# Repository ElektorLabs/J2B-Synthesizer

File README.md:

J2B Synthesizer
===============

An open source, open hardware music synthesizer for you to enjoy.
Based on an LPC1347 32-bit ARM Cortex-M3 microcontroller, this synthesizer
uses PWM to output sound. Originally based on and inspired by the Soulsby
Atmegatron.

Software is an LPCXpresso project.

Precompiled binaries are included for several synthesizers including
one drum machine. Uploading the firmware to the microcontroller is as simple 
as copying a file to a USB stick (this works on Windows only).

Licensed as described in the diverse licenses that may be found in the
repository. Roughly they state that you are allowed to do whatever you want
with this, as long as it remains for private use. However, you are allowed
to make money from music made with the J2B Synthesizer. 

More info:

www.elektor-labs.com/j2b-synthesizer

This is Elektor project 140182, published in Elektor Magazine, January 2015.

www.elektor-magazine.com/140182

www.elektor.com

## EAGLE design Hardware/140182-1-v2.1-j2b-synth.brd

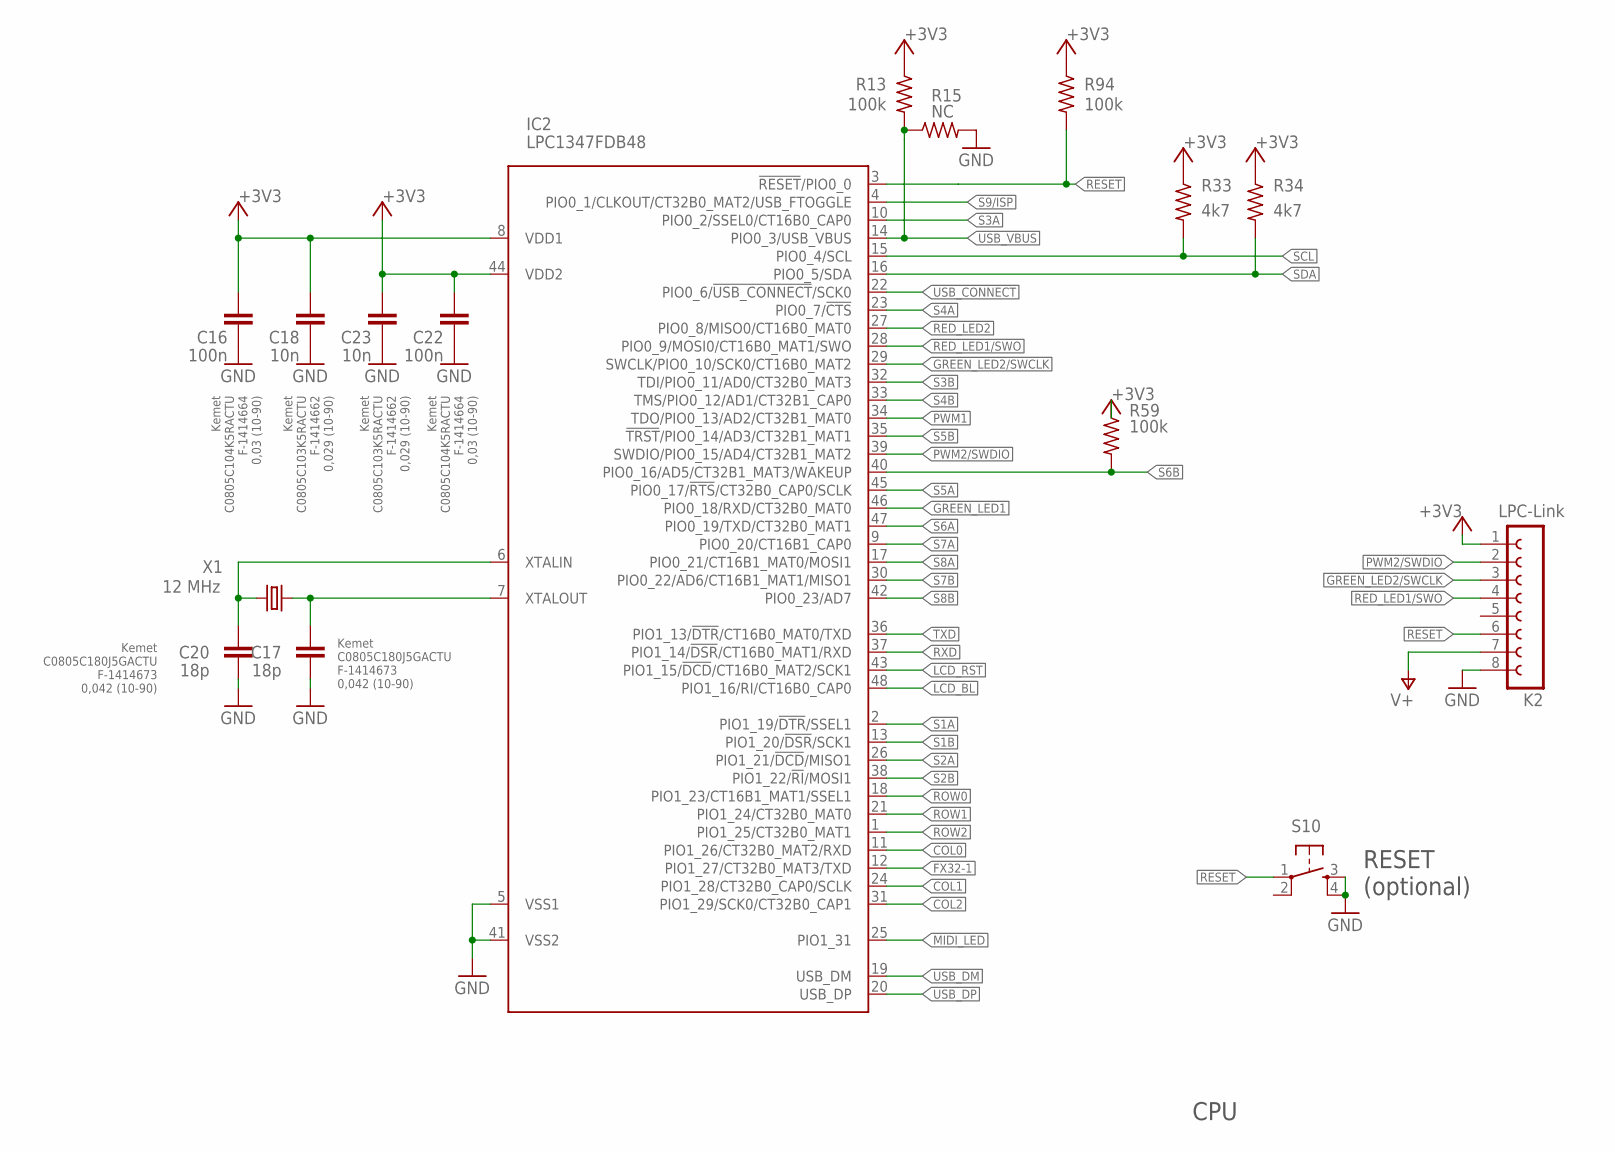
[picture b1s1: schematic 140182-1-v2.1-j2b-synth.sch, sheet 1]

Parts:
C16, C22: 100n; C0805K; FARNELL F-1414664
C17, C20: 18p; C0805K; FARNELL F-1414673
C18, C23: 10n; C0805K; FARNELL F-1414662
IC2: LPC1347FDB48; LQFP48
K2: LPC-Link; FE08
R13, R59, R94: 100k; R0805; FARNELL F-9333738
R15: NC; R0805
R33, R34: 4k7; R0805; FARNELL F-9334580
S10: S-TACTILE-6X6-PTH; EPP-S-TACT-6X6
X1: 12 MHz; SM49

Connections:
!GREEN_LED1!: IC2.46 (PIO0_18/RXD/CT32B0_MAT0); also elsewhere on the board
!GREEN_LED2!/SWCLK: IC2.29 (SWCLK/PIO0_10/SCK0/CT16B0_MAT2), K2.3; also elsewhere on the board
!LCD_BL: IC2.48 (PIO1_16/RI/CT16B0_CAP0); also elsewhere on the board
!RED_LED1!/SWO: IC2.28 (PIO0_9/MOSI0/CT16B0_MAT1/SWO), K2.4; also elsewhere on the board
!RED_LED2: IC2.27 (PIO0_8/MISO0/CT16B0_MAT0); also elsewhere on the board
!RESET: IC2.3 (!RESET!/PIO0_0), K2.6, R94.2, S10.1
!USB_CONNECT: IC2.22 (PIO0_6/!USB_CONNECT!/SCK0); also elsewhere on the board
+3V3: C16.2, C18.2, C22.2, C23.2, IC2.8 (VDD1), IC2.44 (VDD2), K2.1, R13.1, R33.1, R34.1, R59.1, R94.1; also elsewhere on the board
+5V: K2.7; also elsewhere on the board
COL0: IC2.11 (PIO1_26/CT32B0_MAT2/RXD); also elsewhere on the board
COL1: IC2.24 (PIO1_28/CT32B0_CAP0/SCLK); also elsewhere on the board
COL2: IC2.31 (PIO1_29/SCK0/CT32B0_CAP1); also elsewhere on the board
FX32-1: IC2.12 (PIO1_27/CT32B0_MAT3/TXD); also elsewhere on the board
GND: C16.1, C17.1, C18.1, C20.1, C22.1, C23.1, IC2.5 (VSS1), IC2.41 (VSS2), K2.8, R15.2, S10.3, S10.4; also elsewhere on the board
LCD_RST: IC2.43 (PIO1_15/!DCD!/CT16B0_MAT2/SCK1); also elsewhere on the board
MIDI_LED: IC2.25 (PIO1_31); also elsewhere on the board
unnamed: C20.2, IC2.6 (XTALIN), X1.1
unnamed: C17.2, IC2.7 (XTALOUT), X1.2
PWM1: IC2.34 (TDO/PIO0_13/AD2/CT32B1_MAT0); also elsewhere on the board
PWM2/SWDIO: IC2.39 (SWDIO/PIO0_15/AD4/CT32B1_MAT2), K2.2; also elsewhere on the board
ROW0: IC2.18 (PIO1_23/CT16B1_MAT1/SSEL1); also elsewhere on the board
ROW1: IC2.21 (PIO1_24/CT32B0_MAT0); also elsewhere on the board
ROW2: IC2.1 (PIO1_25/CT32B0_MAT1); also elsewhere on the board
RXD: IC2.37 (PIO1_14/!DSR!/CT16B0_MAT1/RXD); also elsewhere on the board
S1A: IC2.2 (PIO1_19/!DTR!/SSEL1); also elsewhere on the board
S1B: IC2.13 (PIO1_20/!DSR!/SCK1); also elsewhere on the board
S2A: IC2.26 (PIO1_21/!DCD!/MISO1); also elsewhere on the board
S2B: IC2.38 (PIO1_22/!RI!/MOSI1); also elsewhere on the board
S3A: IC2.10 (PIO0_2/SSEL0/CT16B0_CAP0); also elsewhere on the board
S3B: IC2.32 (TDI/PIO0_11/AD0/CT32B0_MAT3); also elsewhere on the board
S4A: IC2.23 (PIO0_7/!CTS); also elsewhere on the board
S4B: IC2.33 (TMS/PIO0_12/AD1/CT32B1_CAP0); also elsewhere on the board
S5A: IC2.45 (PIO0_17/!RTS!/CT32B0_CAP0/SCLK); also elsewhere on the board
S5B: IC2.35 (!TRST!/PIO0_14/AD3/CT32B1_MAT1); also elsewhere on the board
S6A: IC2.47 (PIO0_19/TXD/CT32B0_MAT1); also elsewhere on the board
S6B: IC2.40 (PIO0_16/AD5/CT32B1_MAT3/WAKEUP), R59.2; also elsewhere on the board
S7A: IC2.9 (PIO0_20/CT16B1_CAP0); also elsewhere on the board
S7B: IC2.30 (PIO0_22/AD6/CT16B1_MAT1/MISO1); also elsewhere on the board
S8A: IC2.17 (PIO0_21/CT16B1_MAT0/MOSI1); also elsewhere on the board
S8B: IC2.42 (PIO0_23/AD7); also elsewhere on the board
S9/ISP: IC2.4 (PIO0_1/CLKOUT/CT32B0_MAT2/USB_FTOGGLE); also elsewhere on the board
SCL: IC2.15 (PIO0_4/SCL), R33.2; also elsewhere on the board
SDA: IC2.16 (PIO0_5/SDA), R34.2; also elsewhere on the board
TXD: IC2.36 (PIO1_13/!DTR!/CT16B0_MAT0/TXD); also elsewhere on the board
USB_DM: IC2.19 (USB_DM); also elsewhere on the board
USB_DP: IC2.20 (USB_DP); also elsewhere on the board
USB_VBUS: IC2.14 (PIO0_3/USB_VBUS), R13.2, R15.1; also elsewhere on the board

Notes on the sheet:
CPU
RESET (optional)

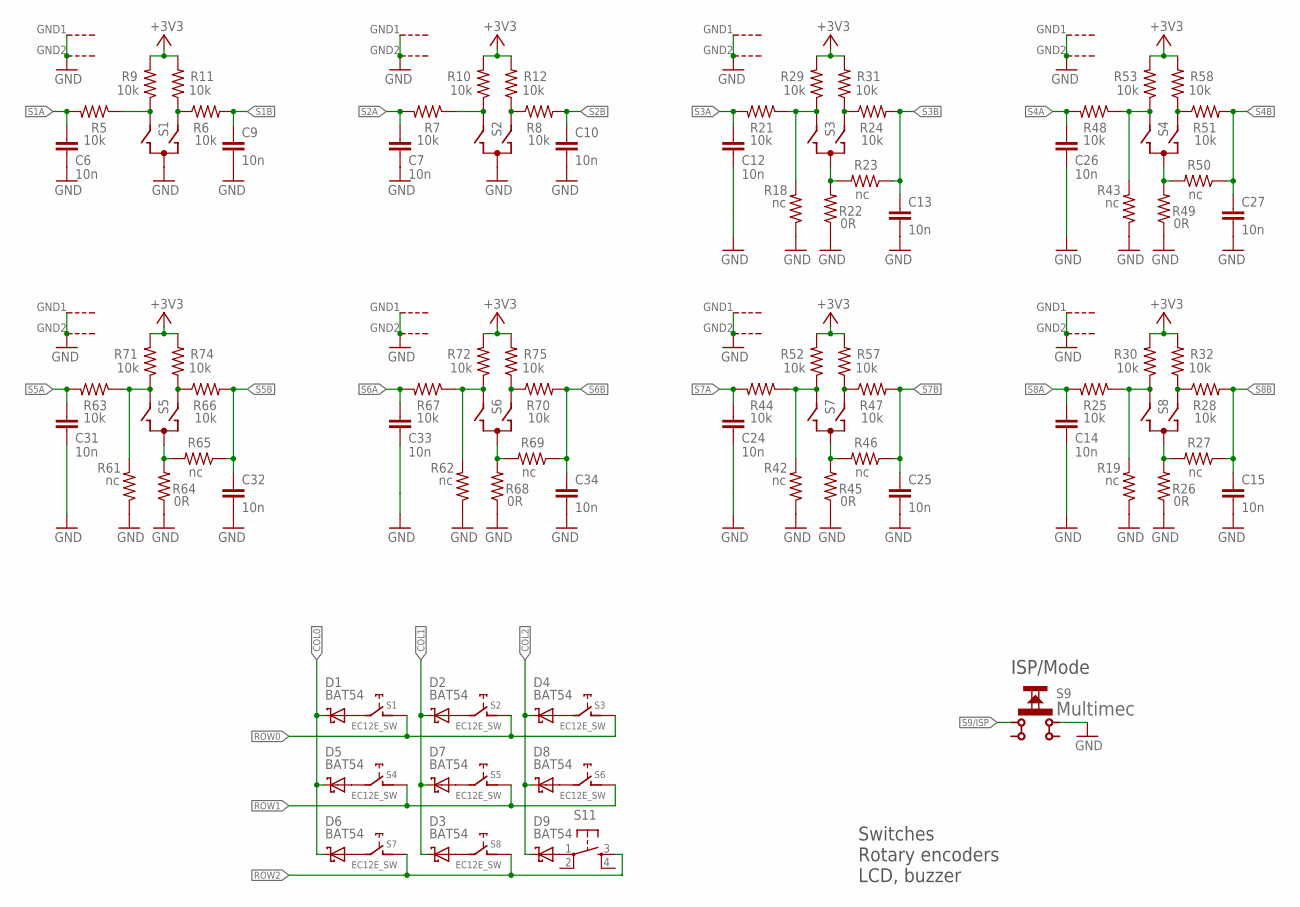
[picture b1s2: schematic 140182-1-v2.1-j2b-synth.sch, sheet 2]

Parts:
C6, C7, C9, C10, C12, C13, C14, C15, C24, C25, C26, C27, C31, C32, C33, C34: 10n; C0805K
D1, D2, D3, D4, D5, D6, D7, D8, D9: BAT54; SOT23
R5, R6, R7, R8, R21, R24, R25, R28, R44, R47, R48, R51, R63, R66, R67, R70: 10k; R0805; FARNELL F-9333711
R9, R10, R11, R12, R29, R30, R31, R32, R52, R53, R57, R58, R71, R72, R74, R75: 10k; R0805; FARNELL F-
R18, R19, R23, R27, R42, R43, R46, R50, R61, R62, R65, R69: nc; R0805; FARNELL F-9333711
R22, R26, R45, R49, R64, R68: 0R; R0805; FARNELL F-9333711
S1, S2, S3, S4, S5, S6, S7, S8: EC12E_SW; ALPS_EC12E_SW
S9: Multimec; PUSHBUTTON_MULTIMEC
S11: S-TACTILE-6X6-PTH; EPP-S-TACT-6X6

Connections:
+3V3: R9.2, R10.2, R11.2, R12.2, R29.2, R30.2, R31.2, R32.2, R52.2, R53.2, R57.2, R58.2, R71.2, R72.2, R74.2, R75.2; also elsewhere on the board
COL0: D1.3 (C), D5.3 (C), D6.3 (C); also elsewhere on the board
COL1: D2.3 (C), D3.3 (C), D7.3 (C); also elsewhere on the board
COL2: D4.3 (C), D8.3 (C), D9.3 (C); also elsewhere on the board
GND: C6.1, C7.1, C9.1, C10.1, C12.1, C13.1, C14.1, C15.1, C24.1, C25.1, C26.1, C27.1, C31.1, C32.1, C33.1, C34.1, R18.1, R19.1, R22.1, R26.1, R42.1, R43.1, R45.1, R49.1, R61.1, R62.1, R64.1, R68.1, S1.C, S1.GND1 (G), S1.GND2 (G), S2.C, S2.GND1 (G), S2.GND2 (G), S3.GND1 (G), S3.GND2 (G), S4.GND1 (G), S4.GND2 (G), S5.GND1 (G), S5.GND2 (G), S6.GND1 (G), S6.GND2 (G), S7.GND1 (G), S7.GND2 (G), S8.GND1 (G), S8.GND2 (G), S9.3; also elsewhere on the board
unnamed: D9.1 (A), S11.1
unnamed: D1.1 (A), S1.E (2)
unnamed: D2.1 (A), S2.E (2)
unnamed: R66.1, R74.1, S5.A
unnamed: R61.2, R63.1, R71.1, S5.B
unnamed: D4.1 (A), S3.E (2)
unnamed: D5.1 (A), S4.E (2)
unnamed: D7.1 (A), S5.E (2)
unnamed: D8.1 (A), S6.E (2)
unnamed: D6.1 (A), S7.E (2)
unnamed: D3.1 (A), S8.E (2)
unnamed: R64.2, R65.2, S5.C
unnamed: R6.1, R11.1, S1.A
unnamed: R5.1, R9.1, S1.B
unnamed: R70.1, R75.1, S6.A
unnamed: R62.2, R67.1, R72.1, S6.B
unnamed: R68.2, R69.2, S6.C
unnamed: R8.1, R12.1, S2.A
unnamed: R7.1, R10.1, S2.B
unnamed: R47.1, R57.1, S7.A
unnamed: R42.2, R44.1, R52.1, S7.B
unnamed: R45.2, R46.2, S7.C
unnamed: R24.1, R31.1, S3.A
unnamed: R18.2, R21.1, R29.1, S3.B
unnamed: R22.2, R23.2, S3.C
unnamed: R28.1, R32.1, S8.A
unnamed: R19.2, R25.1, R30.1, S8.B
unnamed: R26.2, R27.2, S8.C
unnamed: R51.1, R58.1, S4.A
unnamed: R43.2, R48.1, R53.1, S4.B
unnamed: R49.2, R50.2, S4.C
ROW0: S1.D (1), S2.D (1), S3.D (1); also elsewhere on the board
ROW1: S4.D (1), S5.D (1), S6.D (1); also elsewhere on the board
ROW2: S7.D (1), S8.D (1), S11.3; also elsewhere on the board
S1A: C6.2, R5.2; also elsewhere on the board
S1B: C9.2, R6.2; also elsewhere on the board
S2A: C7.2, R7.2; also elsewhere on the board
S2B: C10.2, R8.2; also elsewhere on the board
S3A: C12.2, R21.2; also elsewhere on the board
S3B: C13.2, R23.1, R24.2; also elsewhere on the board
S4A: C26.2, R48.2; also elsewhere on the board
S4B: C27.2, R50.1, R51.2; also elsewhere on the board
S5A: C31.2, R63.2; also elsewhere on the board
S5B: C32.2, R65.1, R66.2; also elsewhere on the board
S6A: C33.2, R67.2; also elsewhere on the board
S6B: C34.2, R69.1, R70.2; also elsewhere on the board
S7A: C24.2, R44.2; also elsewhere on the board
S7B: C25.2, R46.1, R47.2; also elsewhere on the board
S8A: C14.2, R25.2; also elsewhere on the board
S8B: C15.2, R27.1, R28.2; also elsewhere on the board
S9/ISP: S9.1 (2); also elsewhere on the board

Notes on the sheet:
Switches
Rotary encoders
LCD, buzzer
ISP/Mode

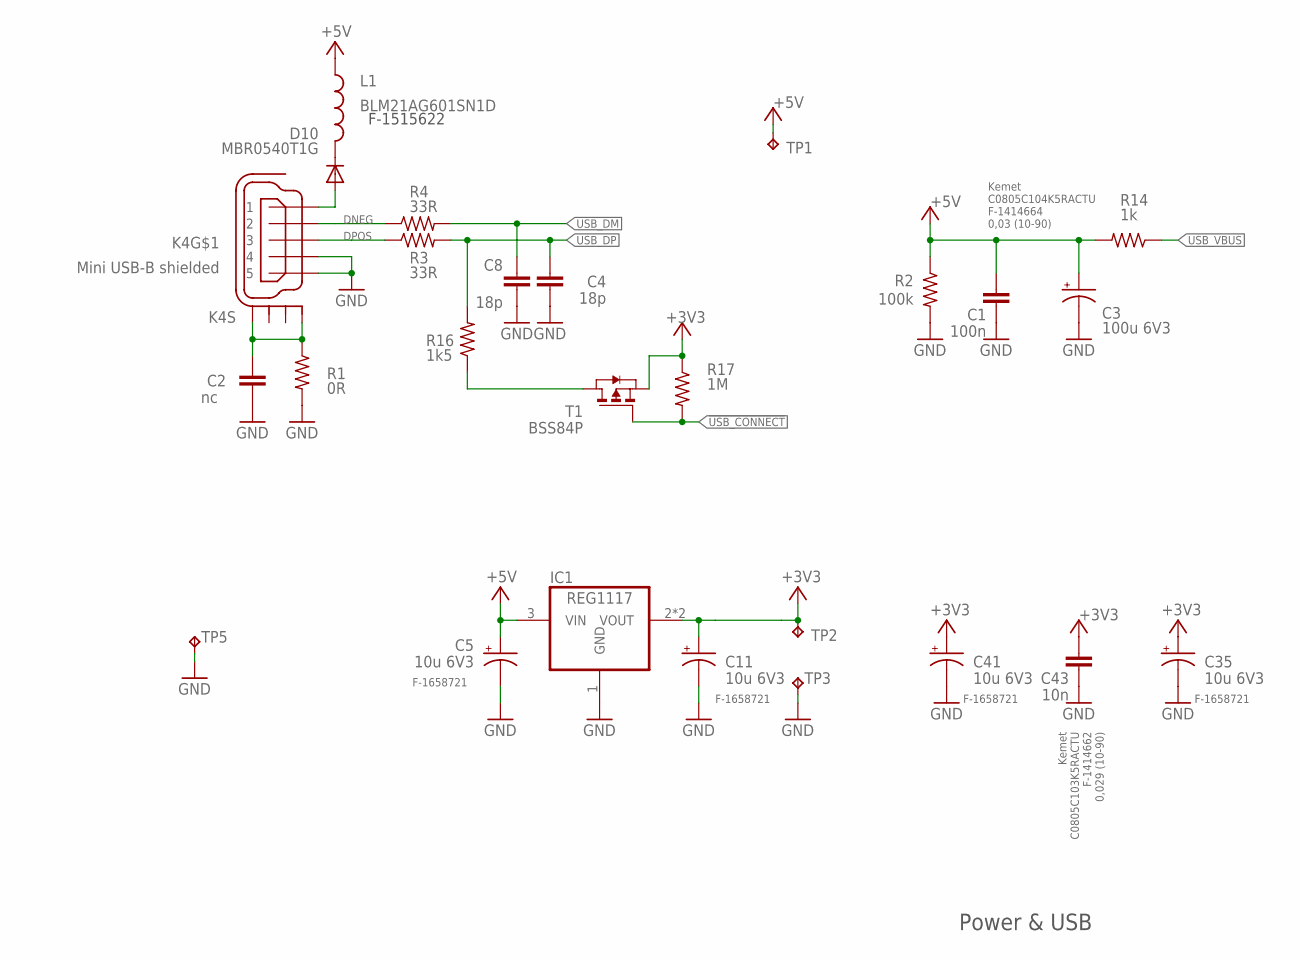
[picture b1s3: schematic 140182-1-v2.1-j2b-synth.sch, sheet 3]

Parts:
C1: 100n; C0805K; FARNELL F-1414664
C2: nc; C0805K
C3: 100u 6V3; B/3528-21R; FARNELL F-1754068
C4, C8: 18p; C0805K
C5, C11, C35, C41: 10u 6V3; SMC_Z; FARNELL F-1658721
C43: 10n; C0805K; FARNELL F-1414662
D10: MBR0540T1G; SOD123
IC1: REG1117; SOT223
K4: Mini USB-B shielded; USB-MINI-B; FARNELL F-1125348
L1: BLM21AG601SN1D; 0805
R1: 0R; R0805; FARNELL F-1576156
R2: 100k; R0805; FARNELL F-9333738
R3, R4: 33R; R0805
R14: 1k; R0805; FARNELL F-9333711
R16: 1k5; R0805
R17: 1M; R0805
T1: BSS84P; SOT-23
TP1, TP2, TP3, TP5: TPPAD1-13; P1-13

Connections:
!USB_CONNECT: R17.2, T1.3 (G); also elsewhere on the board
+3V3: C11.+, C35.+, C41.+, C43.2, IC1.2 (VOUT), IC1.4 (VOUT), R17.1, T1.2 (S), TP2.TP; also elsewhere on the board
+5V: C1.2, C3.+, C5.+, IC1.3 (VIN), L1.2, R2.1, R14.2, TP1.TP; also elsewhere on the board
DNEG: K4.2, R4.1
DPOS: K4.3, R3.1
GND: C1.1, C2.2, C3.-, C4.2, C5.-, C8.2, C11.-, C35.-, C41.-, C43.1, IC1.1 (GND), K4.4, K4.5, R1.2, R2.2, TP3.TP, TP5.TP; also elsewhere on the board
unnamed: D10.C, L1.1
unnamed: C2.1, K4.M1 (S1), K4.M4 (S4), R1.1
unnamed: D10.A, K4.1
unnamed: R16.1, T1.1 (D)
USB_DM: C8.1, R4.2; also elsewhere on the board
USB_DP: C4.1, R3.2, R16.2; also elsewhere on the board
USB_VBUS: R14.1; also elsewhere on the board

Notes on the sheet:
Power & USB
F-1515622

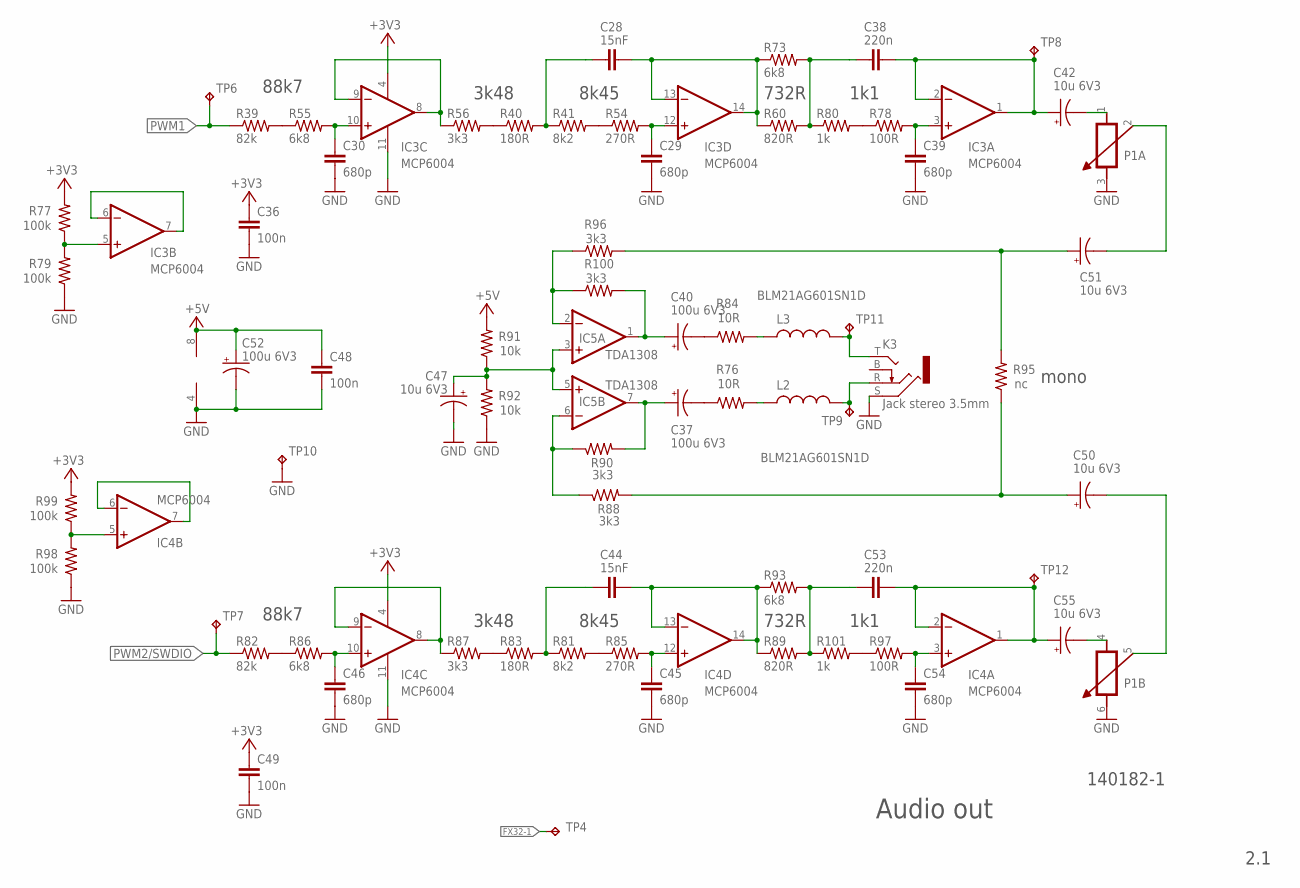
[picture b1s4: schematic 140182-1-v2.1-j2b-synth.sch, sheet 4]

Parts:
C28, C44: 15nF; C0805K
C29, C30, C39, C45, C46, C54: 680p; C0805K
C36, C48, C49: 100n; C0805K
C37, C40, C52: 100u 6V3; B/3528-21R
C38, C53: 220n; C0805K
C42, C47, C50, C51, C55: 10u 6V3; SMC_Z; FARNELL F-1658721
IC3, IC4: MCP6004; SO14
IC5: TDA1308; SO08
K3: Jack stereo 3.5mm; EPP-JACK-35
L2, L3: BLM21AG601SN1D; 0805
P1: POT-BOURNS-PDT90; POT-BOURNS-PTD90-2-WAY
R39, R82: 82k; R0805
R40, R83: 180R; R0805
R41, R81: 8k2; R0805
R54, R85: 270R; R0805
R55, R73, R86, R93: 6k8; R0805
R56, R87: 3k3; R0805
R60, R89: 820R; R0805
R76, R84: 10R; R0805; FARNELL F-9333711
R77, R79, R98, R99: 100k; R0805
R78, R97: 100R; R0805
R80, R101: 1k; R0805
R88, R90, R96, R100: 3k3; R0805; FARNELL F-9333711
R91, R92: 10k; R0805; FARNELL F-9333711
R95: nc; R0805; FARNELL F-9333711
TP4, TP6, TP7, TP8, TP9, TP10, TP11, TP12: TPPAD1-13; P1-13

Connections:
+3V3: C36.1, C49.1, IC3.4 (V+), IC4.4 (V+), R77.2, R99.2; also elsewhere on the board
+5V: C48.1, C52.+, IC5.8 (V+), R91.2; also elsewhere on the board
CH1: C38.2, C42.+, IC3.1 (OUT), IC3.2 (-IN), TP8.TP
CH2: C53.2, C55.+, IC4.1 (OUT), IC4.2 (-IN), TP12.TP
FX32-1: TP4.TP; also elsewhere on the board
GND: C29.2, C30.2, C36.2, C39.2, C45.2, C46.2, C47.-, C48.2, C49.2, C52.-, C54.2, IC3.11 (V-), IC4.11 (V-), IC5.4 (V-), K3.S, P1.3 (B), P1.6 (B), R79.1, R92.1, R98.1, TP10.TP; also elsewhere on the board
HPIN1: C51.+, R95.2, R96.2
HPIN2: C50.+, R88.2, R95.1
unnamed: IC5.2 (-IN), R96.1, R100.1
unnamed: C40.+, IC5.1 (OUT), R100.2
unnamed: L3.2, R84.2
unnamed: L2.2, R76.2
unnamed: C40.-, R84.1
unnamed: C37.-, R76.1
unnamed: C46.1, IC4.10 (+IN), R86.2
unnamed: IC5.6 (-IN), R88.1, R90.1
unnamed: C37.+, IC5.7 (OUT), R90.2
unnamed: IC4.8 (OUT), IC4.9 (-IN), R87.1
unnamed: C45.1, IC4.12 (+IN), R85.2
unnamed: C44.2, IC4.13 (-IN), IC4.14 (OUT), R89.1, R93.1
unnamed: C54.1, IC4.3 (+IN), R97.2
unnamed: R82.2, R86.1
unnamed: R83.1, R87.2
unnamed: R81.2, R85.1
unnamed: R97.1, R101.2
unnamed: C44.1, R81.1, R83.2
unnamed: C53.1, R89.2, R93.2, R101.1
unnamed: C55.-, P1.4 (A)
unnamed: C42.-, P1.1 (A)
unnamed: C47.+, IC5.3 (+IN), IC5.5 (+IN), R91.1, R92.2
unnamed: IC4.5 (+IN), R98.2, R99.1
unnamed: IC4.6 (-IN), IC4.7 (OUT)
unnamed: C30.1, IC3.10 (+IN), R55.2
unnamed: IC3.8 (OUT), IC3.9 (-IN), R56.1
unnamed: C29.1, IC3.12 (+IN), R54.2
unnamed: C28.2, IC3.13 (-IN), IC3.14 (OUT), R60.1, R73.1
unnamed: C39.1, IC3.3 (+IN), R78.2
unnamed: R39.2, R55.1
unnamed: R40.1, R56.2
unnamed: R41.2, R54.1
unnamed: R78.1, R80.2
unnamed: C28.1, R40.2, R41.1
unnamed: C38.1, R60.2, R73.2, R80.1
unnamed: IC3.5 (+IN), R77.1, R79.2
unnamed: IC3.6 (-IN), IC3.7 (OUT)
OUT1: K3.T, L3.1, TP11.TP
OUT2: K3.R, L2.1, TP9.TP
P1AW: C51.-, P1.2 (WIPER)
P1BW: C50.-, P1.5 (WIPER)
PWM1: R39.1, TP6.TP; also elsewhere on the board
PWM2/SWDIO: R82.1, TP7.TP; also elsewhere on the board

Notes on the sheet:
Audio out
88k7
3k48
8k45
732R
1k1
mono

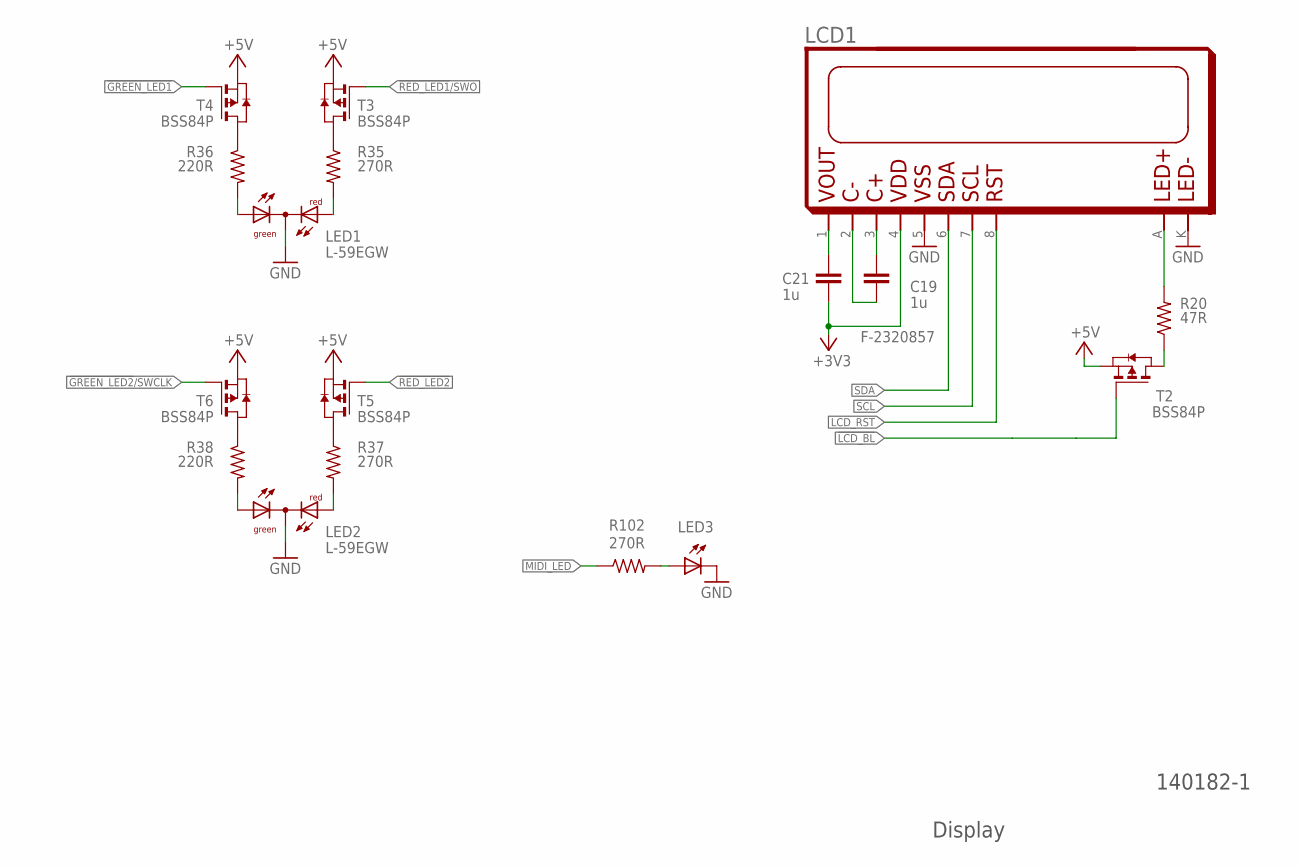
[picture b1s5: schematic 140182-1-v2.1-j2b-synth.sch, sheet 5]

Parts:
C19: 1u; C0805K; FARNELL F-2320857
C21: 1u; C0805K
LCD1: LCD-I2C-MIDAS; LCD-MIDAS-I2C
LED1, LED2: L-59EGW; DUOLED-C-5MM; FARNELL 2001770
LED3: LED3MM
R20: 47R; R1206; FARNELL F-1576615
R35, R37, R102: 270R; R0805; FARNELL F-1576615
R36, R38: 220R; R0805; FARNELL F-1576615
T2, T3, T4, T5, T6: BSS84P; SOT-23

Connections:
!GREEN_LED1!: T4.3 (G); also elsewhere on the board
!GREEN_LED2!/SWCLK: T6.3 (G); also elsewhere on the board
!LCD_BL: T2.3 (G); also elsewhere on the board
!RED_LED1!/SWO: T3.3 (G); also elsewhere on the board
!RED_LED2: T5.3 (G); also elsewhere on the board
+3V3: C21.2, LCD1.4; also elsewhere on the board
+5V: T2.2 (S), T3.2 (S), T4.2 (S), T5.2 (S), T6.2 (S); also elsewhere on the board
GND: LCD1.5, LCD1.K, LED1.C, LED2.C, LED3.K (C); also elsewhere on the board
LCD_RST: LCD1.8; also elsewhere on the board
MIDI_LED: R102.1; also elsewhere on the board
unnamed: LED1.AX (AG), R36.2
unnamed: R36.1, T4.1 (D)
unnamed: C21.1, LCD1.1
unnamed: LED1.AR, R35.2
unnamed: C19.1, LCD1.3
unnamed: C19.2, LCD1.2
unnamed: R35.1, T3.1 (D)
unnamed: LED2.AX (AG), R38.2
unnamed: R38.1, T6.1 (D)
unnamed: LED3.A, R102.2
unnamed: LED2.AR, R37.2
unnamed: R37.1, T5.1 (D)
unnamed: R20.1, T2.1 (D)
unnamed: LCD1.A, R20.2
SCL: LCD1.7; also elsewhere on the board
SDA: LCD1.6; also elsewhere on the board

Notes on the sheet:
Display

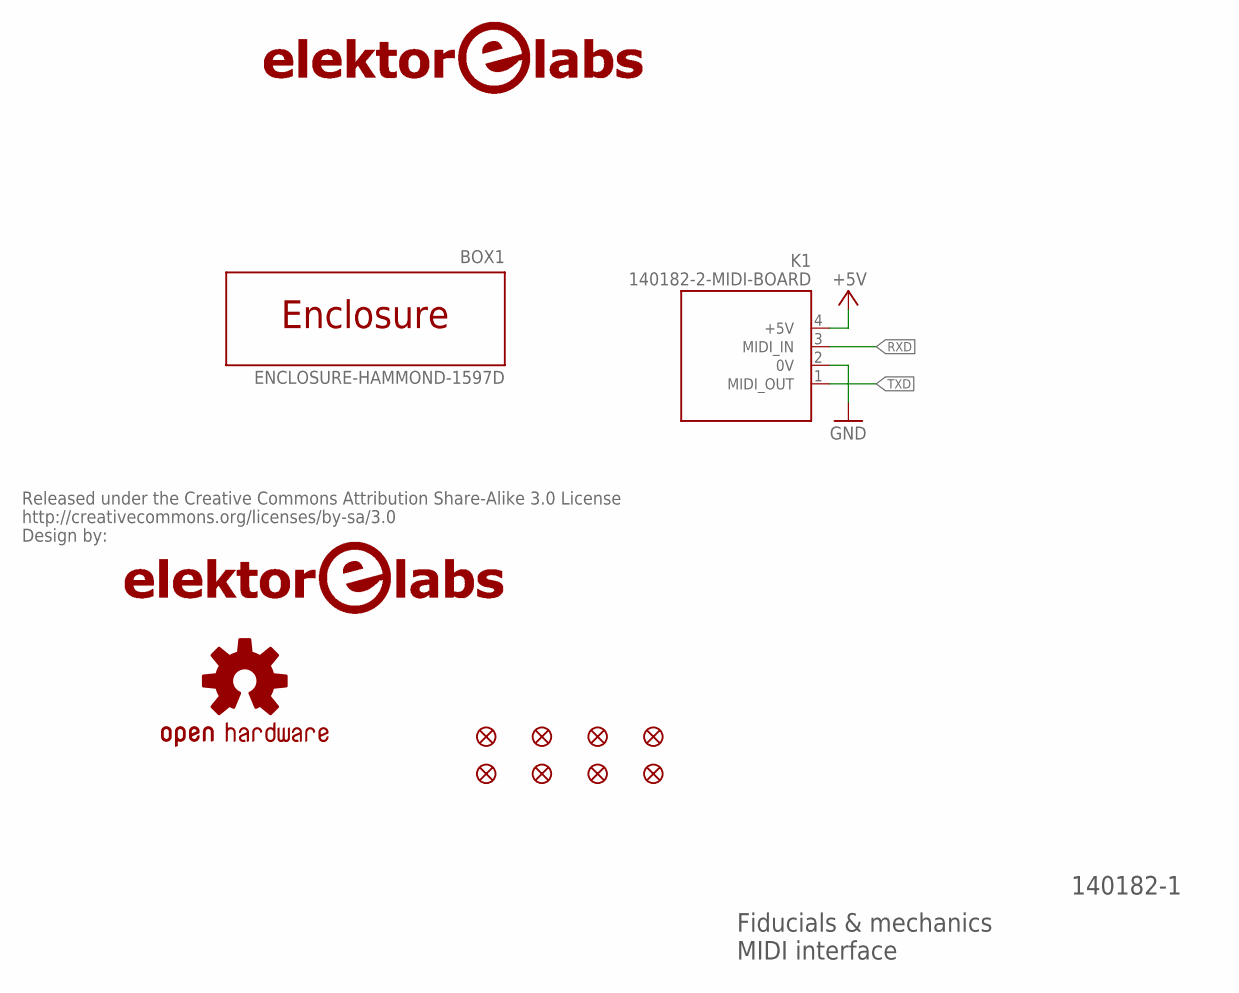
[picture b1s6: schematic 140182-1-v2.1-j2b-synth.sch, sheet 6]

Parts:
BOX1: ENCLOSURE-HAMMOND-1597D; HAMMOND-1597DGY
FID1, FID2, FID3, FID4, FID5, FID6, FID7, FID8: FIDUCIAL1.5X3; FIDUCIAL-1.5X3
K1: 140182-2-MIDI-BOARD; 140182-2-MIDI_BOARD
LOGO1, LOGO2: LOGO-ELEKTOR-LABS-42MM; EPP-LOGO-ELEKTOR-LABS-42MM
U$1: OSHW-LOGOL; OSHW-LOGO-L
U$2: CREATIVE_COMMONS

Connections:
+5V: K1.4 (+5V); also elsewhere on the board
GND: K1.2 (0V); also elsewhere on the board
RXD: K1.3 (MIDI_IN); also elsewhere on the board
TXD: K1.1 (MIDI_OUT); also elsewhere on the board

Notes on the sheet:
Fiducials & mechanics
MIDI interface

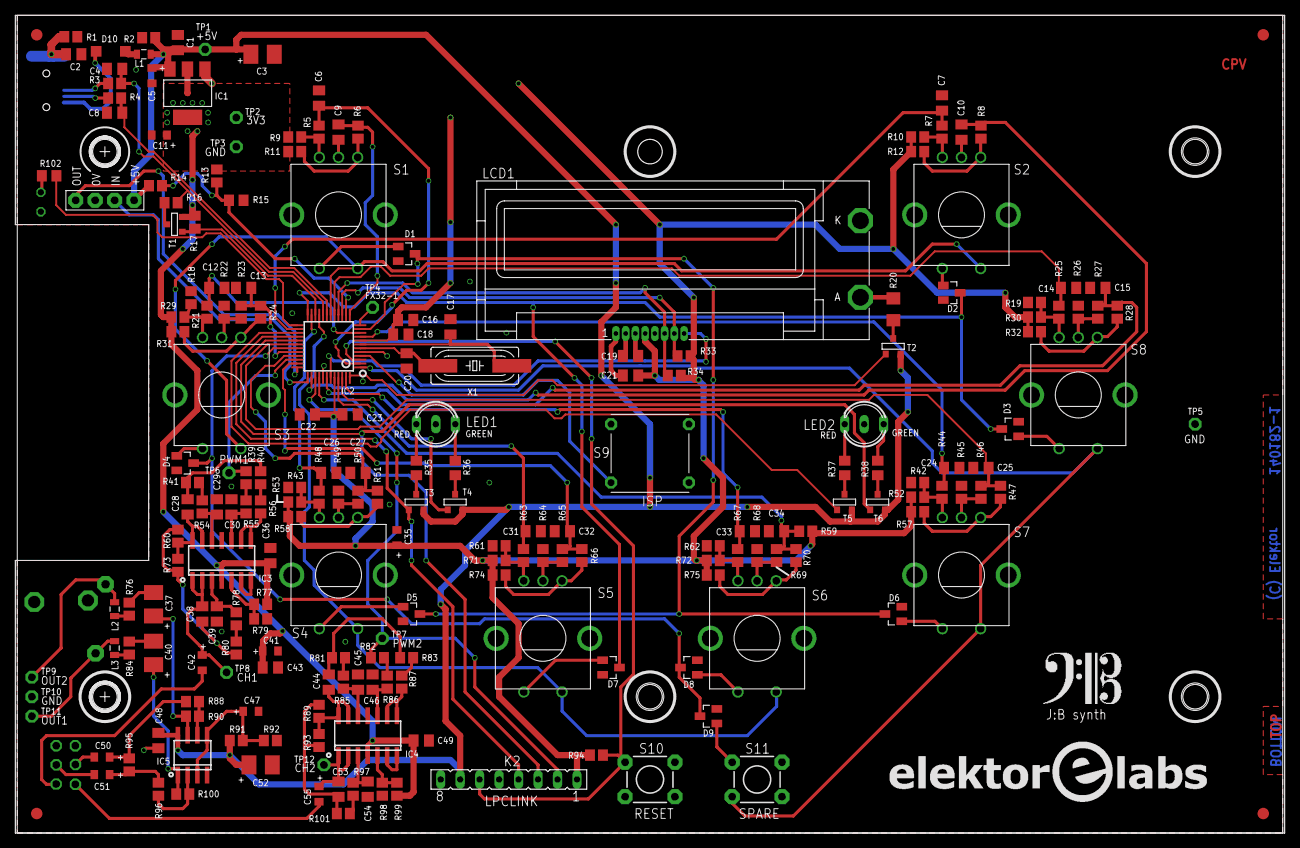
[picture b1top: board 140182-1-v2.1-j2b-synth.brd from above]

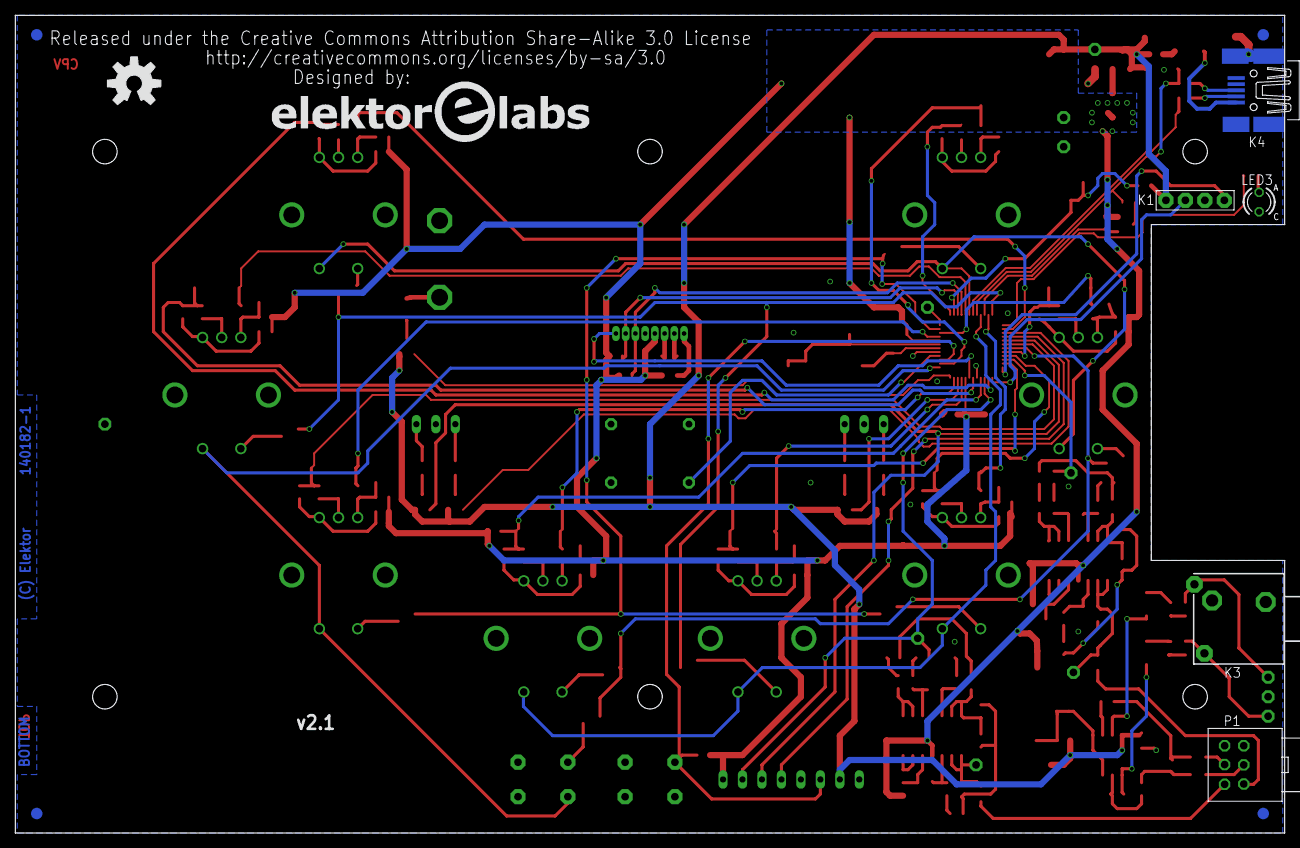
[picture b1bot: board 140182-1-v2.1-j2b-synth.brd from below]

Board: 2 copper layers, 165.6 x 106.7 mm, 227 parts (11 on the bottom side), 143 nets.

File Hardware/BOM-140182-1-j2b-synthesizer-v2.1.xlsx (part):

BOM::140182::J2B-synthesizer::v2.0
Description | Manufacturer | Reference | Footprint | Designation | Qnt | Farnell | Digikey | RS | Price | BOM for editors
Resistor |  |  |  |  | 89 |  |  |  |  | Resistor
resistor 0R 5% 0.1W | Multicomp | MC0805S8F0000T5E | R0805 | R1, R22, R26, R45, R49, R64, R68 | 7 | 2309112 |  |  |  | R1, R22, R26, R45, R49, R64, R68 = resistor 0R 5% 0.1W
resistor 10R 5% 0.1W | Multicomp | MC 0.1W 0805 5% 10R | M0805 | R76, R84 | 2 | 9333690 |  |  |  | R76, R84 = resistor 10R 5% 0.1W
resistor 33R 5% 0.1W | Multicomp | MC 0.1W 0805 5% 33R | R0805 | R3, R4 | 2 | 9334343 |  |  |  | R3, R4 = resistor 33R 5% 0.1W
resistor 47R 5% 0.25W | Multicomp | MCSR12X470 JTL | R1206 | R20 | 1 | 2074656 |  |  |  | R20 = resistor 47R 5% 0.25W
resistor 100R 5% 0.1W | Multicomp | MC01W08055100R | R0805 | R78, R97 | 2 | 9333703 |  |  |  | R78, R97 = resistor 100R 5% 0.1W
resistor 180R 5% 0.1W | Multicomp | MC01W08055180R | R0805 | R40, R83 | 2 | 9334025 |  |  |  | R40, R83 = resistor 180R 5% 0.1W
resistor 220R 5% 0.1W | Multicomp | MC01W08055220R | R0805 | R36, R38 | 2 | 9334130 |  |  |  | R36, R38 = resistor 220R 5% 0.1W
resistor 270R 5% 0.1W | Multicomp | MC01W08055270R | R0805 | R35, R37, R54, R85, R102 | 5 | 9334254 |  |  |  | R35, R37, R54, R85, R102 = resistor 270R 5% 0.1W
resistor 820R 5% 0.1W | Multicomp | MC01W08055820R | R0805 | R60, R89 | 2 | 9334890 |  |  |  | R60, R89 = resistor 820R 5% 0.1W
resistor 1k 5% 0.1W | Multicomp | MC 0.1W 0805 5% 1K | R0805 | R14, R80, R101 | 3 | 9333711 |  |  |  | R14, R80, R101 = resistor 1k 5% 0.1W
resistor 1k5 5% 0.1W | Multicomp | MC 0.1W 0805 5% 1K5 | R0805 | R16 | 1 | 9333924 |  |  |  | R16 = resistor 1k5 5% 0.1W
resistor 3k3 5% 0.1W | Multicomp | MC01W080553K3 | R0805 | R56, R87, R88, R90, R96, R100 | 6 | 9334360 |  |  |  | R56, R87, R88, R90, R96, R100 = resistor 3k3 5% 0.1W
resistor 4k7 5% 0.1W | Multicomp | MC 0.1W 0805 5% 4K7 | R0805 | R33, R34 | 2 | 9334580 |  |  |  | R33, R34 = resistor 4k7 5% 0.1W
resistor 6k8 5% 0.1W | Multicomp | MC01W080556K8 | R0805 | R55, R73, R86, R93 | 4 | 9334793 |  |  |  | R55, R73, R86, R93 = resistor 6k8 5% 0.1W
resistor 8k2 5% 0.1W | Multicomp | MC01W080558K2 | R0805 | R41, R81 | 2 | 9334904 |  |  |  | R41, R81 = resistor 8k2 5% 0.1W
resistor 10k 5% 0.1W | Multicomp | MC 0.1W 0805 5% 10K | R0805 | R5, R6, R7, R8, R9, R10, R11, R12, R21, R24, R25, R28, R29, R30, R31, R32, R44,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 | 34 | 9333720 |  |  |  | R5, R6, R7, R8, R9, R10, R11, R12, R21, R24, R25, R28, R29, R30, R31, R32, R44,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
resistor 82k 5% 0.1W | Multicomp | MC01W0805582K | R0805 | R39, R82 | 2 | 9334912 |  |  |  | R39, R82 = resistor 82k 5% 0.1W
resistor 100k 5% 0.1W | Multicomp | MC 0.1W 0805 5% 100K | R0805 | R2, R13, R59, R77, R79, R94, R98, R99 | 8 | 9333738 |  |  |  | R2, R13, R59, R77, R79, R94, R98, R99 = resistor 100k 5% 0.1W
resistor 1M 5% 0.1W | Multicomp | MC 0.1W 0805 5% 1M | R0805 | R17 | 1 | 9333746 |  |  |  | R17 = resistor 1M 5% 0.1W
Potentiometer 10k log stereo | Bourns | PTD902-2015F-A103 | POT-STEREO | P1 | 1 | 2396034 |  |  |  | P1 = Potentiometer 10k log stereo
NC |  |  |  | R15, R18, R19, R23, R27, R42, R43, R46, R50, R61, R62, R65, R69, R95 |  |  |  |  |  | R15, R18, R19, R23, R27, R42, R43, R46, R50, R61, R62, R65, R69, R95 = NC
Capacitor |  |  |  |  | 54 |  |  |  |  | Capacitor
capacitor 18pF NPO 50V | Kemet | C0805C180J5GACTU | C0805K | C4, C8, C17, C20 | 4 | 1414673 |  |  |  | C4, C8, C17, C20 = capacitor 18pF NPO 50V
capacitor 680pF NPO 50V | Multicomp | MC0805N681J101CT | C0805K | C29, C30, C39, C45, C46, C54 | 6 | 1759286 |  |  |  | C29, C30, C39, C45, C46, C54 = capacitor 680pF NPO 50V
capacitor 10nF X7R 50V | Kemet | C0805C103K5RACTU | C0805K | C6, C7, C9, C10, C12, C13, C14, C15, C18, C23, C24, C25, C26, C27, C31, C32, C3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 | 19 | 1414662 |  |  |  | C6, C7, C9, C10, C12, C13, C14, C15, C18, C23, C24, C25, C26, C27, C31, C32, C3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
capacitor 15nF X7R 50V | Multicomp | MC0805B153K500CT | C0805K | C28, C44 | 2 | 1759249 |  |  |  | C28, C44 = capacitor 15nF X7R 50V
capacitor 100nF X7R 50V | Kemet | C0805C104K5RACTU | C0805K | C1, C16, C22, C36, C48, C49 | 6 | 1414664 |  |  |  | C1, C16, C22, C36, C48, C49 = capacitor 100nF X7R 50V
capacitor 220nF X7R 50V | Kemet | C0805C224K5RACTU | C0805K | C38, C53 | 2 | 1288261 |  |  |  | C38, C53 = capacitor 220nF X7R 50V
capacitor 1uF X7R 10V | Multicomp | MC0805B105K100CT | C0805K | C19, C21 | 2 | 2320857 |  |  |  | C19, C21 = capacitor 1uF X7R 10V
capacitor tantalum 10uF 6.3V | AVX | TPSR106K006R1500 | 0805 | C5, C11, C35, C41, C42, C47, C50, C51, C55 | 9 | 1658721 |  |  |  | C5, C11, C35, C41, C42, C47, C50, C51, C55 = capacitor tantalum 10uF 6.3V
capacitor tantalum 100uF 6.3V | Vishay Sprague | TR3B107M6R3C1500 | B/3528-21R | C3, C37, C40, C52 | 4 | 1754048 |  |  |  | C3, C37, C40, C52 = capacitor tantalum 100uF 6.3V
NC |  |  | C0805K | C2 |  |  |  |  |  | C2 = NC
Inductor / Self |  |  |  |  | 3 |  |  |  |  | Inductor / Self
Ferrite bead, 0.21Ω, 0.6A | Murata | BLM21AG601SN1D | L0805 | L1, L2, L3 | 3 | 1515622 |  |  |  | L1, L2, L3 = Ferrite bead, 0.21Ω, 0.6A
Semiconductor |  |  |  |  | 24 |  |  |  |  | Semiconductor
BAT54C,215 | NXP | BAT54C,215 | SOT-23 | D1, D2, D3, D4, D5, D6, D7, D8, D9 | 9 | 1081192 |  |  |  | D1, D2, D3, D4, D5, D6, D7, D8, D9 = BAT54C,215
MBR0540T1G | ON Semiconductor | MBR0540T1G | SOD-123 | D10 | 1 | 9556923 |  |  |  | D10 = MBR0540T1G
LED, bi-color, red-green, CC, 5mm | Kingbright | L-59EGW | DUOLED-C-5MM | LED1, LED2 | 2 | 2001770 |  |  |  | LED1, LED2 = LED, bi-color, red-green, CC, 5mm
LED, red, 3mm | Multicomp | MCL034MT | EPP-LED-3MM | LED3 | 1 | 1581122 |  |  |  | LED3 = LED, red, 3mm
LPC1347FBD48 | NXP | LPC1347FBD48 | LQFP48 | IC2 | 1 | 2103477 |  | 791-8179 |  | IC2 = LPC1347FBD48
LD1117S33CTR | STMicroelectronics | LD1117S33CTR | SOT223 | IC1 | 1 | 1467779 |  |  |  | IC1 = LD1117S33CTR
BSS84P | Infineon | BSS84P | SOT-23 | T1, T2, T3, T4, T5, T6 | 6 | 1056526 |  |  |  | T1, T2, T3, T4, T5, T6 = BSS84P
MCP6004-I/SL | Microchip | MCP6004-I/SL | SOIC14 | IC3, IC4 | 2 | 1605572 |  |  |  | IC3, IC4 = MCP6004-I/SL
TDA1308T/N2 | NXP | TDA1308T/N2 | SOIC8 | IC5 | 1 | 1854038 |  |  |  | IC5 = TDA1308T/N2
Misc. |  |  |  |  | 17 |  |  |  |  | Misc.
header male 4 pin, 0.1" pitch vertical | Fisher Elektronik | SL1.025.4Z | through-hole 2.54 mm pitch single row | K1 | 1 | 9729038 |  |  |  | K1 = header male 4 pin, 0.1" pitch vertical
header male 8 pin, 0.1" pitch vertical | Fisher Elektronik | SL1.025.8Z | through-hole 2.54 mm pitch single row | K2 | 1 | 9729038 |  |  |  | K2 = header male 8 pin, 0.1" pitch vertical
Jack 3.5 mm, stereo | Lumberg | KLBR 4 | EPP-JACK-350 | K3 | 1 | 1217016 |  |  |  | K3 = Jack 3.5 mm, stereo
Mini USB-B shielded | Molex | 675031020 | 0.8" SMD Mini-USB-B | K4 | 1 | 1125348 |  |  |  | K4 = Mini USB-B shielded
Rotary encoder | Alps | EC12E2424407 | through-hole | S1, S2, S3, S4, S5, S6, S7, S8 | 8 | 1520813 |  |  |  | S1, S2, S3, S4, S5, S6, S7, S8 = Rotary encoder
Push button | Multimec | 3FTL6 | through-hole | S9 | 1 | 1132885 |  |  |  | S9 = Push button
LCD 2x16, I²C | Midas | MCCOG21605B6W-SPTLYI | LCD-I2C | LCD1 | 1 | 2063208 |  |  |  | LCD1 = LCD 2x16, I²C
crystal 12 MHz | IQD Frequency Products | LF A158E | HC49/SMD | X1 | 1 | 9713344 |  |  |  | X1 = crystal 12 MHz
Enclosure | Hammond | 1597DGY | n/a | BOX1 | 1 | 1876944 |  |  |  | BOX1 = Enclosure
PCB 140182-1-v2.1 | Elektor |  |  |  | 1 |  |  |  |  | PCB 140182-1-v2.1
3FTL6 |  |  | PUSHBUTTON_MULTIMEC | S1 |  |  |  |  |  | PUSHBUTTON_MULTIMEC
3FTL6 |  |  | PUSHBUTTON_MULTIMEC | S2 |  |  |  |  |  | PUSHBUTTON_MULTIMEC
3FTL6 |  |  | PUSHBUTTON_MULTIMEC | S3 |  |  |  |  |  | PUSHBUTTON_MULTIMEC
3FTL6 |  |  | PUSHBUTTON_MULTIMEC | S4 |  |  |  |  |  | PUSHBUTTON_MULTIMEC
3FTL6 |  |  | PUSHBUTTON_MULTIMEC | S5 |  |  |  |  |  | PUSHBUTTON_MULTIMEC
3FTL6 |  |  | PUSHBUTTON_MULTIMEC | S6 |  |  |  |  |  | PUSHBUTTON_MULTIMEC
3FTL6 |  |  | PUSHBUTTON_MULTIMEC | S7 |  |  |  |  |  | PUSHBUTTON_MULTIMEC
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
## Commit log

2015-06-04 :lollipop: Added .gitattributes & .gitignore files
2015-06-04 Now at GitHub
    Firmware starts at V3.0
    Hardware starts at V2.1
    Mechanics start at V3.0

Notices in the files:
Hardware/140182-1-v2.1-j2b-synth.brd:
COPYRIGHT: (C) Elektor
parts and their libraries:
140182-1-v2.0-j2b-synth: Released under the Creative Commons Attribution Share-Alike 3.0 License
140182-1-v2.0-j2b-synth: http://creativecommons.org/licenses/by-sa/3.0
SparkFun-Aesthetics: Licensing: CC v3.0 Share-Alike You are welcome to use this library for commercial purposes.
